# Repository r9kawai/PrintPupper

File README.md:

# PrintPupper  
## Release v0.2 2025 Aug 14
PrintPupper is an open-source quadruped robot that anyone can build. It is based on Pupper, developed by Stanford University, and has been redesigned to be cheaper and easier to build. With just a 3D printer and inexpensive parts, you can build a full-fledged quadruped robot with 12 joints.  
PrintPupper は誰でも作れるオープンソースの四足歩行ロボットです。スタンフォード大学の開発したPupperを元に、より安価に簡単に作れるよう再設計しました。3Dプリンタと安価な部品だけで12自由度の本格四足ロボを作れます。

## printpupper.com  
[https://www.printpupper.com/](https://www.printpupper.com/)  
This portal site explains the assembly procedure with detailed figs.
このポータルサイトでは組立手順を詳細な図で説明しています。
  
・3DプリンターとAmazonで容易に入手できる安価な部品だけで作れる。  
・組立手順をWebで詳細に説明。  
・FreeCAD設計データ、KiCAD基板設計データなど全てGitHubで公開。  
・オリジナル設計よりも頑丈で壊れにくい。  
・USBジョイパッド対応。  
・キャリブレーション作業がジョイパッドだけで可能。  
・RC用大容量バッテリー搭載可能で40分の連続歩行。  
・拡張性あり、改造が容易、IMU搭載が可能。  
・Raspberry Pi 3以降または、Raspberry Pi Zero 2 W での作成が可能。  
  
・Can be built using only a 3D printer and inexpensive parts readily available on Amazon.  
・Assembly instructions are explained in detail on the Web.  
・FreeCAD design data, KiCAD board design data, etc. are all available on GitHub.  
・Sturdier and less likely to break than the original design.  
・Compatible with USB joypad.  
・Calibration can be done using only the joypad.  
・Can be equipped with a large-capacity RC battery for 40 minutes of continuous walking.  
・Expandable, easy to modify, and can be equipped with an IMU.  
・Can be built with a Raspberry Pi 3 or later, or a Raspberry Pi Zero 2 W.

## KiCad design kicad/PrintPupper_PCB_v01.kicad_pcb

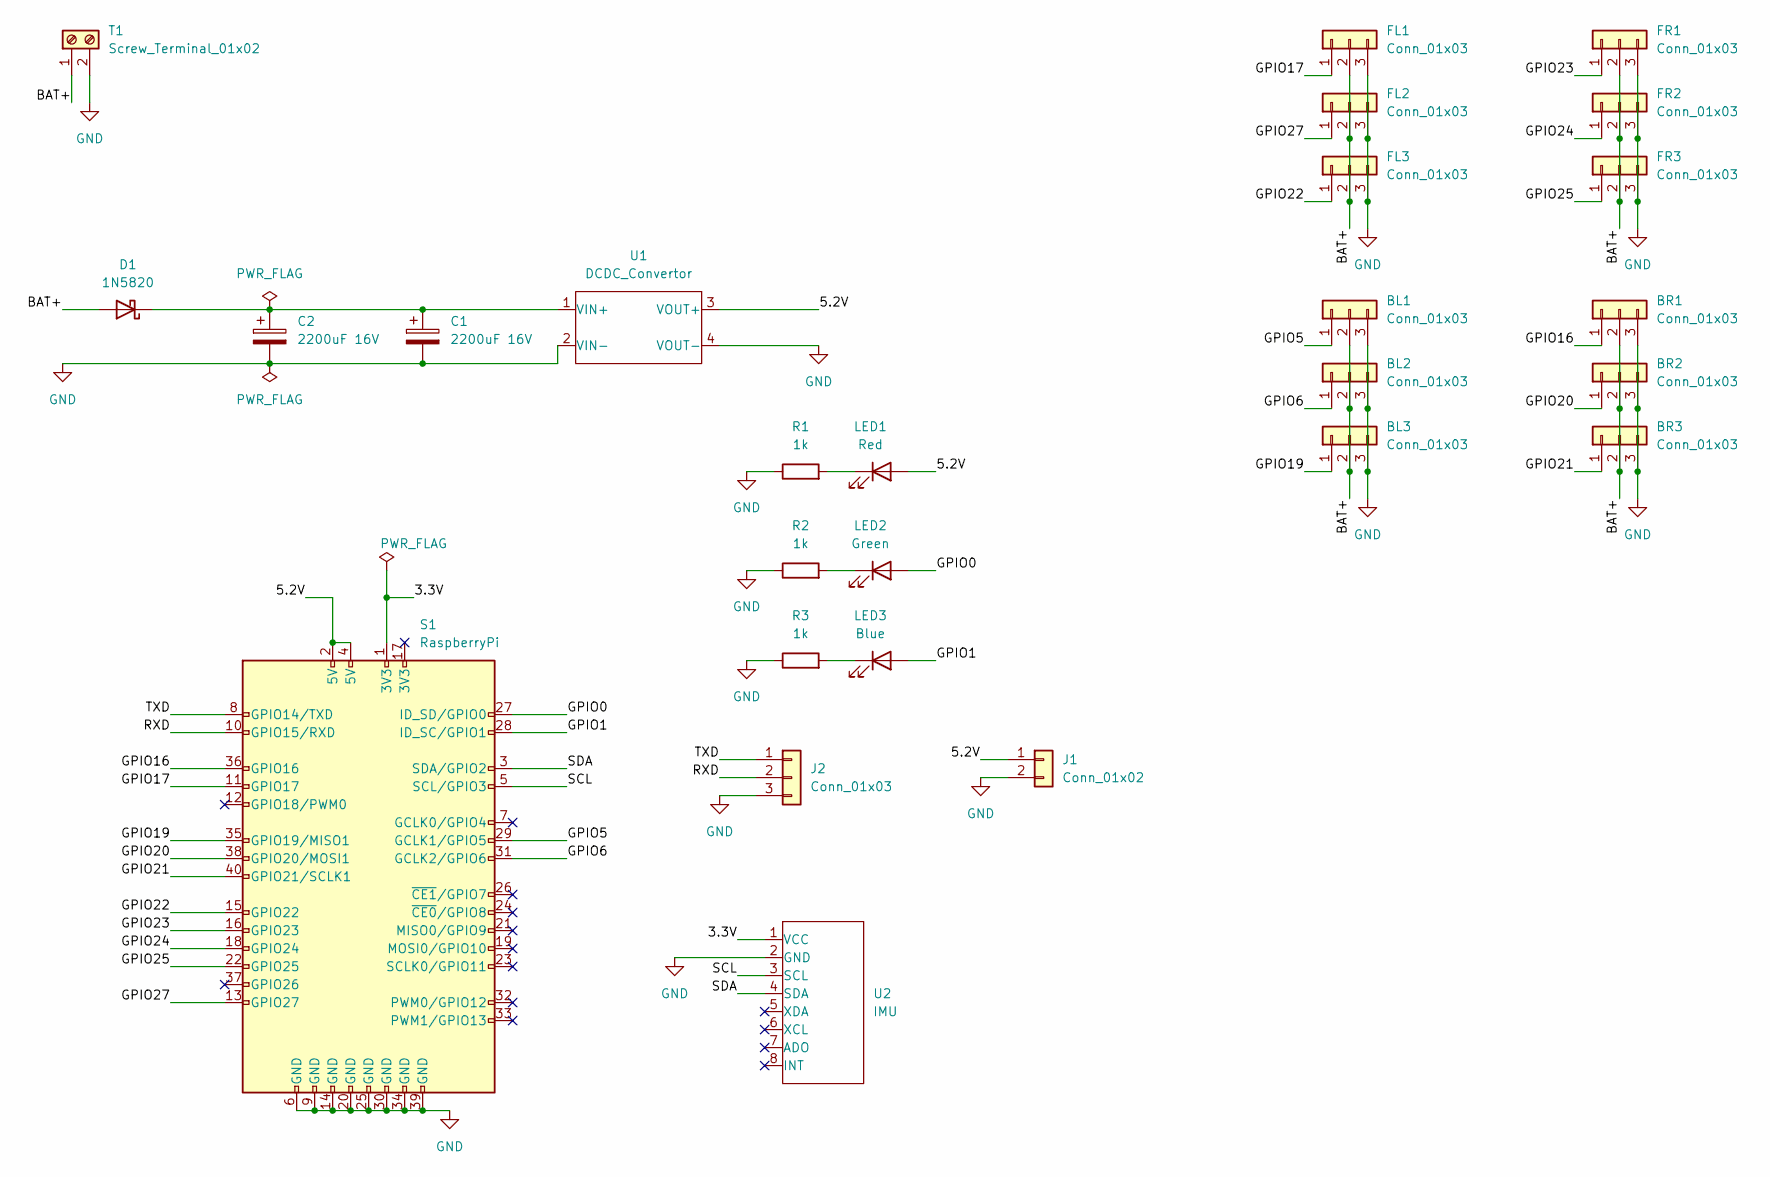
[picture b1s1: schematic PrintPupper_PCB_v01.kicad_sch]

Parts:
BL1, BL2, BL3: Conn_01x03; PinHeader_1x3P2.54mm
BR1, BR2, BR3: Conn_01x03; PinHeader_1x3P2.54mm
C1, C2: 2200uF 16V; CP_Radial_D10.0mm_P5.00mm
D1: 1N5820; D_DO-201AD_P5.08mm_Vertical_AnodeUp
FL1, FL2, FL3: Conn_01x03; PinHeader_1x3P2.54mm
FR1, FR2, FR3: Conn_01x03; PinHeader_1x3P2.54mm
J1: Conn_01x02; PinHeader_1x2P2.54mm
J2: Conn_01x03; PinHeader_1x3P2.54mm
LED1: Red; LED_D5.0mm
LED2: Green; LED_D5.0mm
LED3: Blue; LED_D5.0mm
R1, R2, R3: 1k; R_Axial_DIN0207_L6.3mm_D2.5mm_P2.54mm_Vertical
S1: RaspberryPi; PinSocket_2x20_P2.54mm_Vertical
T1: Screw_Terminal_01x02; TerminalBlock_2P5.08mm
U1: DCDC_Convertor; module_XL6009_dcdc
U2: IMU; imu_mpu6050

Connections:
/3.3V: S1.1 (3V3), U2.1 (VCC)
/5.2V: J1.1, LED1.2 (A), S1.2 (5V), S1.4 (5V), U1.3 (VOUT+)
/BAT+: BL1.2, BL2.2, BL3.2, BR1.2, BR2.2, BR3.2, D1.2 (A), FL1.2, FL2.2, FL3.2, FR1.2, FR2.2, FR3.2, T1.1
/GPIO0: LED2.2 (A), S1.27 (ID_SD/GPIO0)
/GPIO1: LED3.2 (A), S1.28 (ID_SC/GPIO1)
/GPIO5: BL1.1, S1.29 (GCLK1/GPIO5)
/GPIO6: BL2.1, S1.31 (GCLK2/GPIO6)
/GPIO16: BR1.1, S1.36 (GPIO16)
/GPIO17: FL1.1, S1.11 (GPIO17)
/GPIO19: BL3.1, S1.35 (GPIO19/MISO1)
/GPIO20: BR2.1, S1.38 (GPIO20/MOSI1)
/GPIO21: BR3.1, S1.40 (GPIO21/SCLK1)
/GPIO22: FL3.1, S1.15 (GPIO22)
/GPIO23: FR1.1, S1.16 (GPIO23)
/GPIO24: FR2.1, S1.18 (GPIO24)
/GPIO25: FR3.1, S1.22 (GPIO25)
/GPIO27: FL2.1, S1.13 (GPIO27)
/RXD: J2.2, S1.10 (GPIO15/RXD)
/SCL: S1.5 (SCL/GPIO3), U2.3 (SCL)
/SDA: S1.3 (SDA/GPIO2), U2.4 (SDA)
/TXD: J2.1, S1.8 (GPIO14/TXD)
GND: BL1.3, BL2.3, BL3.3, BR1.3, BR2.3, BR3.3, C1.2, C2.2, FL1.3, FL2.3, FL3.3, FR1.3, FR2.3, FR3.3, J1.2, J2.3, R1.1, R2.1, R3.1, S1.6 (GND), S1.9 (GND), S1.14 (GND), S1.20 (GND), S1.25 (GND), S1.30 (GND), S1.34 (GND), S1.39 (GND), T1.2, U1.2 (VIN-), U1.4 (VOUT-), U2.2 (GND)
unnamed: C1.1, C2.1, D1.1 (K), U1.1 (VIN+)
unnamed: LED1.1 (K), R1.2
unnamed: LED2.1 (K), R2.2
unnamed: LED3.1 (K), R3.2

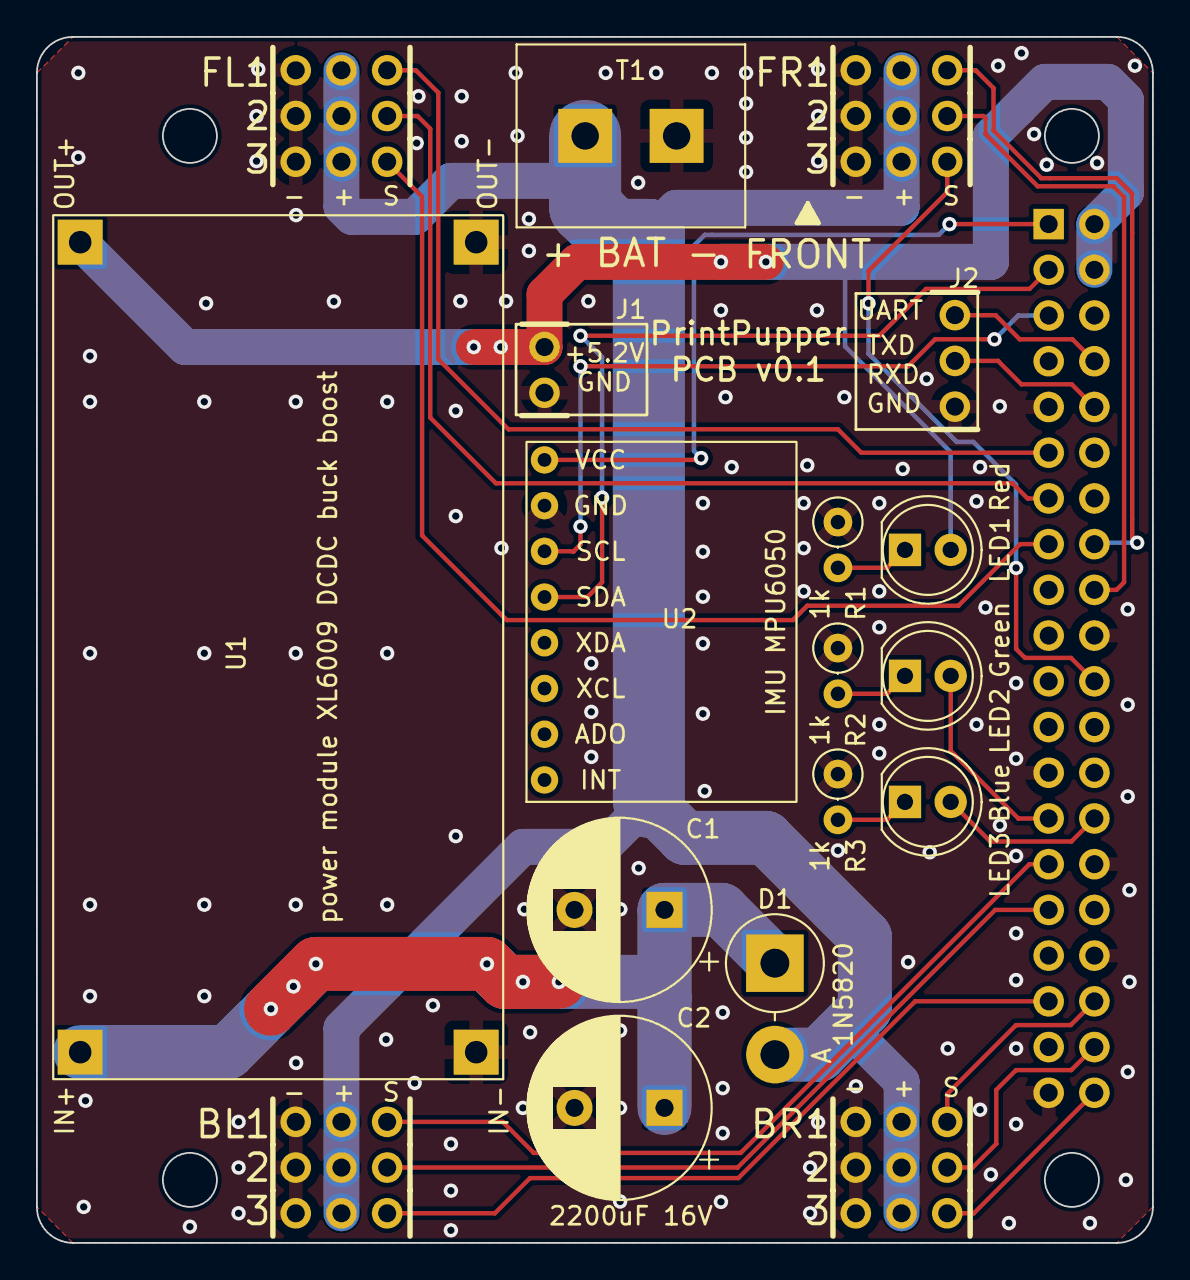
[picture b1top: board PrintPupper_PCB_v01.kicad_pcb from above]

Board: 2 copper layers, 62.0 x 67.0 mm, 27 parts (1 on the bottom side), 26 nets.

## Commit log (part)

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2023-05-26 Create README_md_pic
2023-05-26 add pic1.png
2023-06-04 add paper 0604
2023-06-08 PrintPupper for git public under construction
2023-06-08 amend PrintPupper_design.xlsx
2023-06-13 making_20230614
2023-06-13 making_20230614_2
2023-06-13 amend miss
2023-06-13 making_20230614_3
2023-06-13 making_20230614_4
2023-06-15 making_20230615-1
2023-06-15 making_20230615-2
2023-06-28 making_20230628_1 commit
2023-07-16 making_202307017a
2023-07-16 making_20230717b
2023-07-19 making_20230720_about_servo_pwm
2023-07-20 making_20230720_1
2023-07-25 making_20230725_amend_boot
2023-07-25 making_20230725_amend_boot_services_2
2023-07-26 making_20230726_1_2
2023-07-27 making_20230727_1
2023-07-27 making_20230727_2
2023-07-27 making_20230728_3
2023-07-28 making_20230729_1
2023-07-29 making_20230729_2
2023-07-30 making_20230730_1_2
2023-07-31 making_20230731_1
2023-08-02 making_20230802_1
2023-08-04 making_20230805_1
2023-08-06 making_20230806_1
2023-08-06 making_20230807_1
2023-08-07 making_20230808_1
2023-08-13 making_20230813_1
2023-08-15 making_20230815_1
2023-08-15 making_20230815_2
2023-08-19 tune_20230820_1
2023-09-10 add contents PrintPupper_design.xlsx
2023-09-10 making_20230910_1
2023-09-11 tune_20230911_1
2023-09-11 tune_amend_1
2023-09-11 Raspberry Pi confirm of parts list amend.
2023-09-22 tune_20230923_1
2023-09-22 tune_20230923_2
2023-09-22 tune_20230923_3
2023-09-25 20230925_1
2023-10-01 cycle_tune_20231001_1
2023-10-11 tune_20231011_1
2023-10-11 small debug (out "dt_sleep").
2023-10-23 tag "v0.1 fix" 2023 Oct 23
2023-11-16 acceleration_sensor_opt_11-16
2025-05-27 dev_start_v0.2
2025-05-28 v0.2_dev_0528a
2025-05-28 v0.2_dev_0528b
2025-05-29 v0.2_dev_0529a
2025-05-29 v0.2_dev_0529b
2025-05-29 v0.2_dev_0529c
2025-06-01 v0.2_dev_0601a
2025-06-03 v0.2_dev_0603a
2025-06-04 v0.2_dev_0604a
2025-06-06 v0.2_dev_0606a
2025-06-07 v0.2_dev_0607a
2025-06-13 v0.2_dev_0613a
2025-06-17 v0.2_dev_0618a
2025-06-18 v0.2_dev_0618b
2025-06-18 v0.2_dev_0618c
2025-06-22 v0.2_dev_0622a
2025-06-22 v0.2_dev_0622b
2025-06-23 v0.2_dev_0623a
2025-06-23 v0.2_dev_0623b
2025-06-29 v0.2_dev_0630a
2025-07-01 v0.2_dev_0701a
2025-07-02 v0.2_dev_0702a
2025-07-08 v0.2_dev_0709a
2025-07-15 v0.2_dev_0715a
2025-07-18 v0.2_dev_0718a
2025-07-18 v0.2_dev_0718b
2025-07-19 v0.2_dev_0719a
2025-07-20 v0.2_dev_L1-110mm_0720a
2025-07-20 0720b
2025-07-24 0724_as_soft
2025-07-24 0724_as_mecha
2025-07-25 0725a_as_soft
2025-07-26 0726_as_soft_TemporarilyCompleted
2025-07-27 0727a_as_mecha_UpdateStand
2025-07-28 0728a_as_assembly
2025-08-03 0803a_as_assembly
2025-08-03 0803b_as_soft_setting_script
2025-08-03 0803c_as_soft_setting_script
2025-08-03 0803d_as_soft_setting_script
2025-08-03 0804a_as_soft_setting_script
2025-08-08 0808a_as_soft_calib_ledcolor
2025-08-12 0812_as_mecha_fix_SvHornDowel
2025-08-12 0812_as_soft_fixInstallScript
2025-08-12 0812_organize_files_for_v0.2fix
2025-08-12 0812_add_etc_partLists
2025-09-11 dev_0911a
2025-09-13 dev_0913a
2025-09-14 dev_0914a
2025-09-15 dev_0915a
2025-09-17 dev_0917a
2025-09-25 asCAD_addMountPointsOnFBtorso_fixLowerLegCap
2025-09-25 dev_0925a
2025-09-26 dev_0926a
2025-09-27 dev_0927a
2025-09-27 dev_0927b
2025-09-28 dev_0928a
2025-09-28 dev_0929a
2025-09-30 dev_0930a
2025-10-03 bug_fix_for_F710joypad
2025-10-04 dev_1004a_TriangleBTN_RXLXswitch
2025-10-04 Revert "dev_1004a_TriangleBTN_RXLXswitch"
    This reverts commit 685b18bc9c378a5778ffdda8e991549774d920c6.
2025-10-04 dev_1004b_TriangleBTN_RXLXswitch
2025-10-09 1009_small_fix_as_CAD
2025-11-19 dev_1119a_decoration_parts
2025-12-01 add_exportSTEP_20-27_print_deco
2026-01-30 add_doc_UML_figs
